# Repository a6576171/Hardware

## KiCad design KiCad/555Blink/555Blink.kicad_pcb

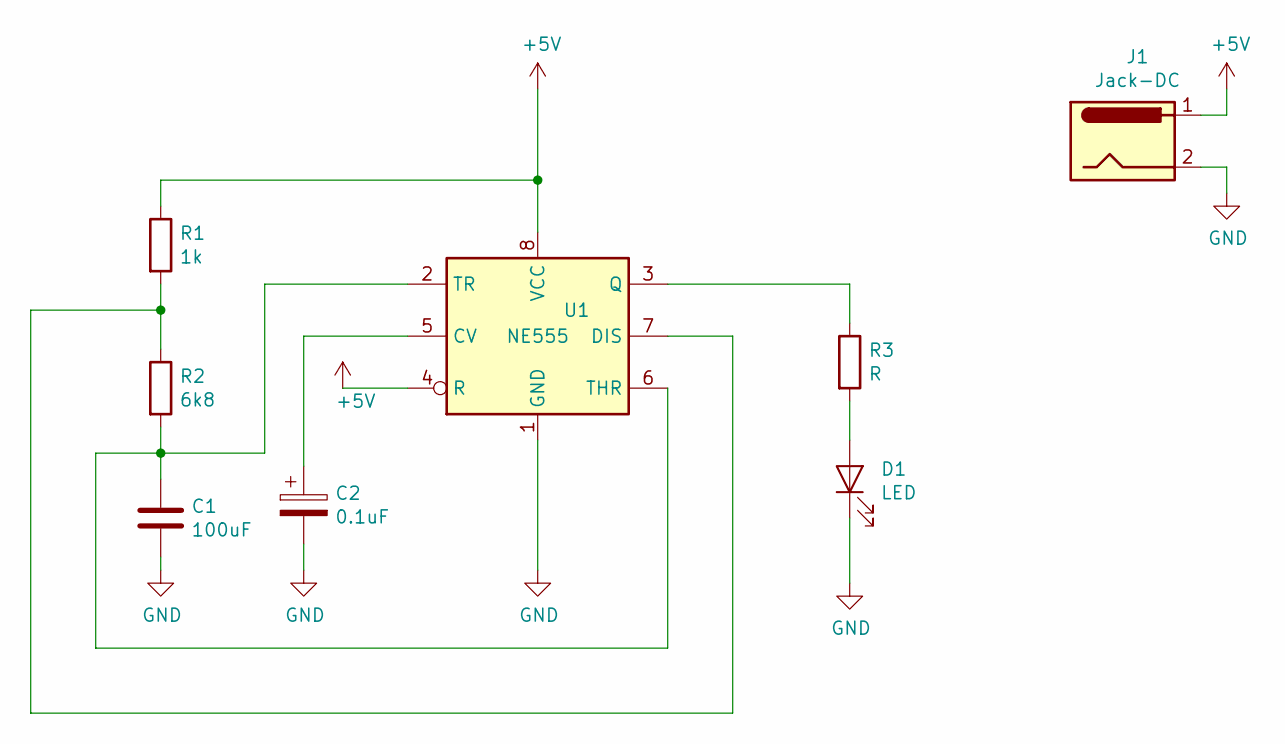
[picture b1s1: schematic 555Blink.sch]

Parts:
C1: 100uF; CP_Radial_D10.0mm_P3.80mm
C2: 0.1uF; C_Disc_D6.0mm_W4.4mm_P5.00mm
D1: LED; LED_D3.0mm
J1: Jack-DC; Molex_KK-254_AE-6410-02A_1x02_P2.54mm_Vertical
R1: 1k; R_Axial_DIN0207_L6.3mm_D2.5mm_P7.62mm_Horizontal
R2: 6k8; R_Axial_DIN0207_L6.3mm_D2.5mm_P7.62mm_Horizontal
R3: R; R_Axial_DIN0207_L6.3mm_D2.5mm_P7.62mm_Horizontal
U1: NE555; DIP-8_W7.62mm_Socket_LongPads

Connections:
+5V: J1.1, R1.1, U1.4 (R), U1.8 (VCC)
GND: C1.2, C2.2, D1.1 (K), J1.2, U1.1 (GND)
unnamed: C1.1, R2.2, U1.2 (TR), U1.6 (THR)
unnamed: C2.1, U1.5 (CV)
unnamed: D1.2 (A), R3.2
unnamed: R1.2, R2.1, U1.7 (DIS)
unnamed: R3.1, U1.3 (Q)

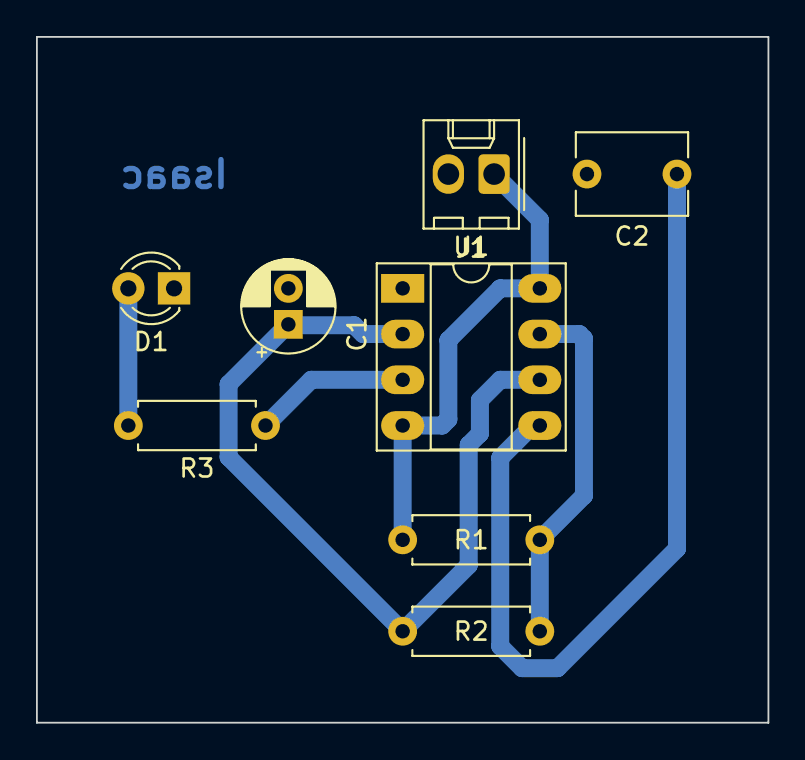
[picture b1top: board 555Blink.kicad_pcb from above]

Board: 2 copper layers, 40.6 x 38.1 mm, 8 parts (0 on the bottom side), 7 nets.

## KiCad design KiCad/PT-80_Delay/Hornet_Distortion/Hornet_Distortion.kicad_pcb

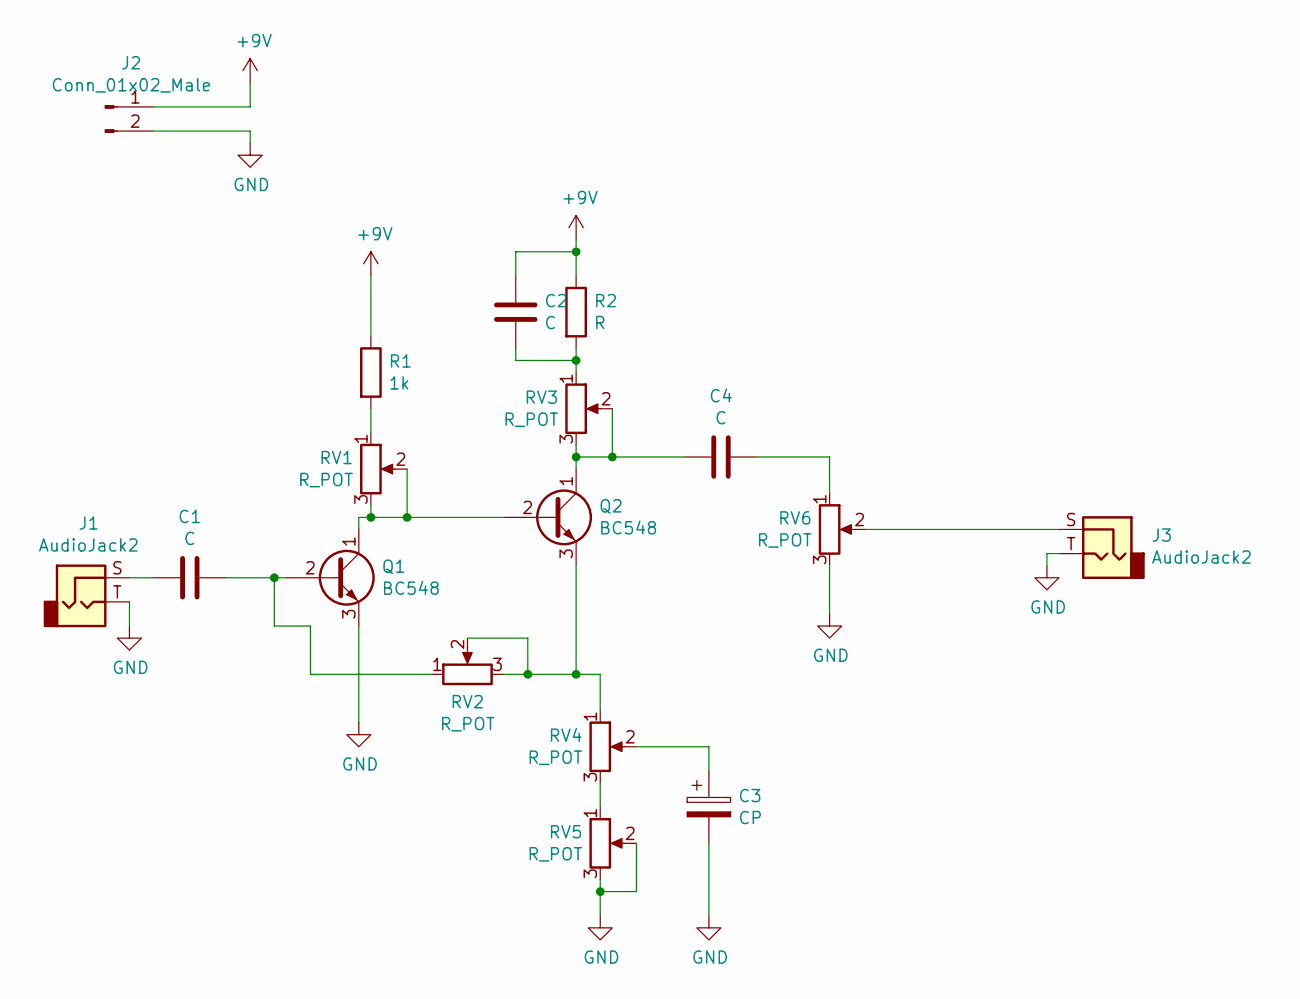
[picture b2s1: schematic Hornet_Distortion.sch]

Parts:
C1, C2, C4: C; C_Disc_D7.5mm_W5.0mm_P5.00mm
C3: CP; CP_Radial_D8.0mm_P3.80mm
J1, J3: AudioJack2; Jack_3.5mm_CUI_SJ-3523-SMT_Horizontal
J2: Conn_01x02_Male; Molex_KK-254_AE-6410-02A_1x02_P2.54mm_Vertical
Q1, Q2: BC548; TO-92L_Inline_Wide
R1: 1k; R_Axial_DIN0207_L6.3mm_D2.5mm_P10.16mm_Horizontal
R2: R; R_Axial_DIN0207_L6.3mm_D2.5mm_P10.16mm_Horizontal
RV1, RV2, RV3, RV4, RV5, RV6: R_POT; Potentiometer_ACP_CA9-H5_Horizontal

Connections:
+9V: C2.2, J2.1, R1.1, R2.1
GND: C3.2, J1.T, J2.2, J3.T, Q1.3 (E), RV5.2, RV5.3, RV6.3
unnamed: C1.1, Q1.2 (B), RV2.1
unnamed: C1.2, J1.S
unnamed: C2.1, R2.2, RV3.1
unnamed: C3.1, RV4.2
unnamed: C4.1, Q2.1 (C), RV3.2, RV3.3
unnamed: C4.2, RV6.1
unnamed: J3.S, RV6.2
unnamed: Q1.1 (C), Q2.2 (B), RV1.2, RV1.3
unnamed: Q2.3 (E), RV2.2, RV2.3, RV4.1
unnamed: R1.2, RV1.1
unnamed: RV4.3, RV5.1

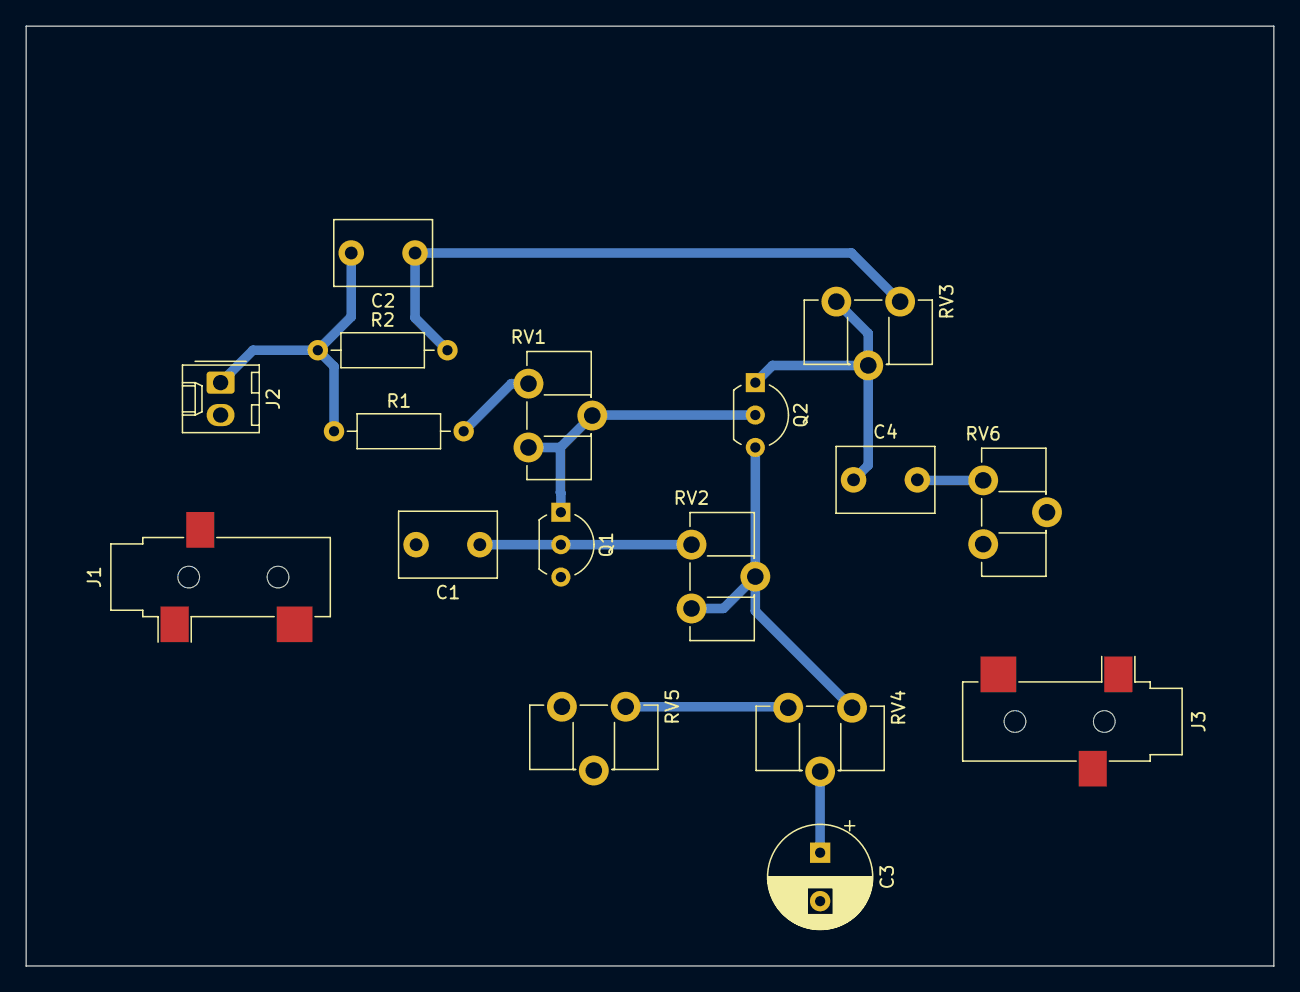
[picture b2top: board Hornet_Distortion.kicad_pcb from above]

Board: 2 copper layers, 97.8 x 73.7 mm, 17 parts (0 on the bottom side), 13 nets.

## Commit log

2019-10-15 Fist
    PNCDF
2020-02-09 Create fp-info-cache
2020-07-02 Funções de exemplo
